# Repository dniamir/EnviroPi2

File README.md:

# EnvriPi sensor hub shield for Raspberry Pi
A Raspberry Pi shield that houses several different types of sensors
-BME280 - Bosch pressure, temperature and humidity sensor
-BME680 - Bosch pressure, humidity, temperature and VOC sensor
-TMP102 - Texas Instruments temperature sensor
-BMM150 - Bosch magnetometer
-TSL25911FN - Light intensity sensor
-ICM-20649 - Invensense 6-axis IMU (3-axis gyroscope and 3-axis accelerometer)

## Summary
This code utlizies high level functions to communicate with sensors and set their configuration for proper monitoring of an aquarium.

Unfortunately, I can't make the sub-repository for chip communication public. However that package provides a simple interface for communicating with sensors va I2C and SPI.

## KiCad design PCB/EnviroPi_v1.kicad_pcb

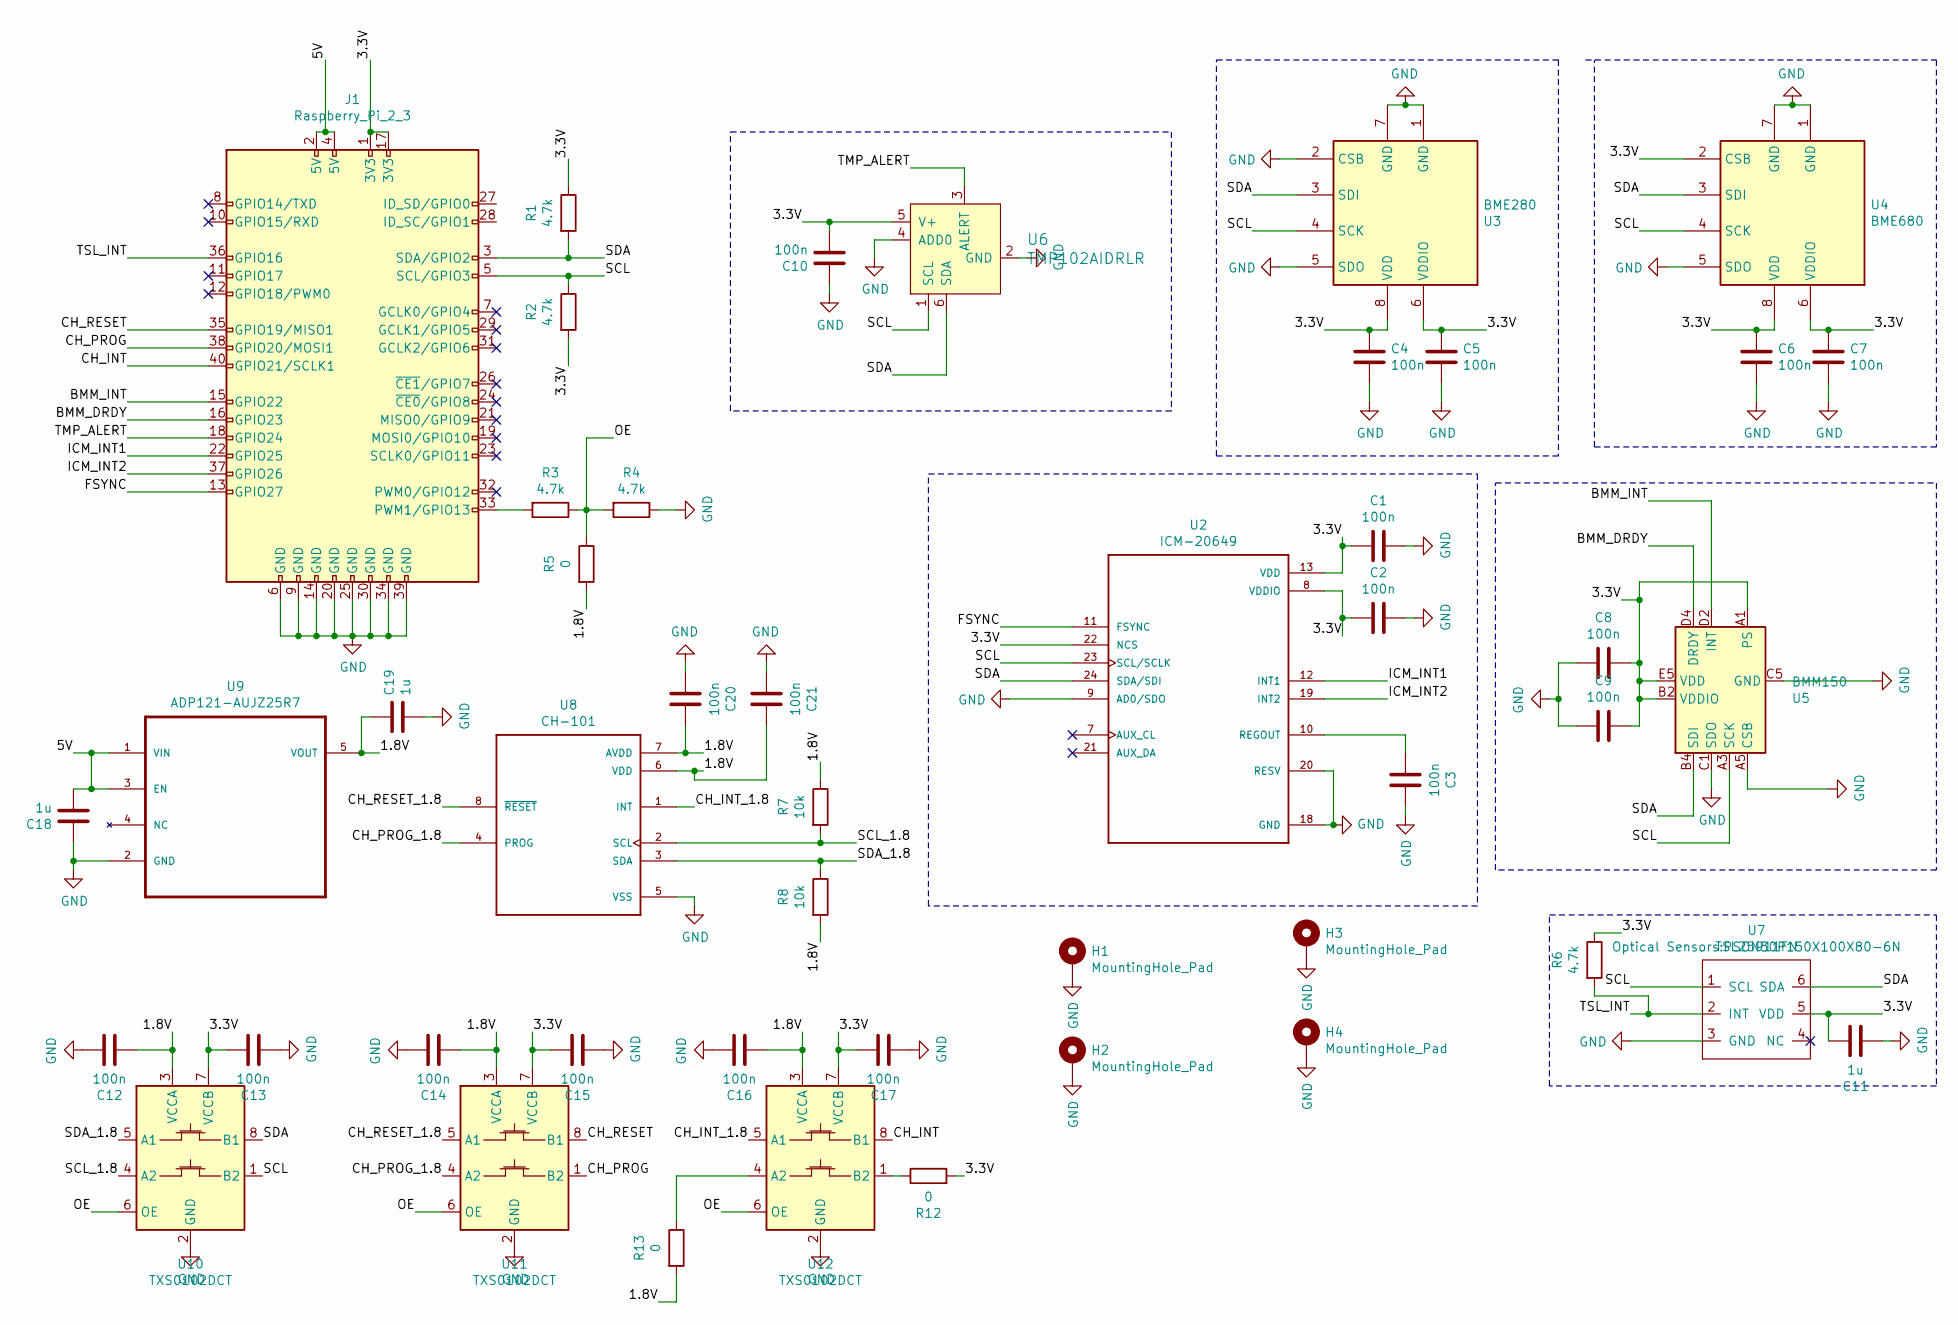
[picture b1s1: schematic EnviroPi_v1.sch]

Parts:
C1, C2, C3, C4, C5, C6, C7, C8, C9, C10, C12, C13, C14, C15, C16, C17, C20, C21: 100n; C_0805_2012Metric_Pad1.15x1.40mm_HandSolder
C11, C18, C19: 1u; C_0805_2012Metric_Pad1.15x1.40mm_HandSolder
H1, H2, H3, H4: MountingHole_Pad; MountingHole_2.5mm_Pad
J1: Raspberry_Pi_2_3; PinHeader_2x20_P2.54mm_Vertical
R1, R2, R3, R4, R6: 4.7k; R_0805_2012Metric_Pad1.15x1.40mm_HandSolder
R5, R12, R13: 0; R_0805_2012Metric_Pad1.15x1.40mm_HandSolder
R7, R8: 10k; R_0805_2012Metric_Pad1.15x1.40mm_HandSolder
U2: ICM-20649; QFN40P300X300X95-24N
U3: BME280; Bosch_LGA-8_2.5x2.5mm_P0.65mm_ClockwisePinNumbering
U4: BME680; Bosch_LGA-8_3x3mm_P0.8mm_ClockwisePinNumbering
U5: BMM150; WLCSP-12_1.56x1.56mm_P0.4mm
U6: TMP102AIDRLR; SOT50P160X60-6N; MPN TMP102AIDRLR; Digi-Key_PN 296-26834-1-ND
U7: TSL25911FN; PSON50P150X100X80-6N
U8: CH-101; XDCR_CH-101
U9: ADP121-AUJZ25R7; SOT95P280X100-5N
U10, U11, U12: TXS0102DCT; SSOP-8_2.95x2.8mm_P0.65mm

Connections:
/1.8V: C12.1, C14.1, C16.1, C19.1, C20.2, C21.2, R5.2, R7.1, R8.2, R13.2, U8.6 (VDD), U8.7 (AVDD), U9.5 (VOUT), U10.3 (VCCA), U11.3 (VCCA), U12.3 (VCCA)
/3.3V: C1.1, C2.1, C4.1, C5.1, C6.1, C7.1, C8.2, C9.2, C10.2, C11.2, C13.2, C15.2, C17.2, J1.1 (3V3), J1.17 (3V3), R1.1, R2.2, R6.1, R12.2, U2.8 (VDDIO), U2.13 (VDD), U2.22 (NCS), U3.6 (VDDIO), U3.8 (VDD), U4.2 (CSB), U4.6 (VDDIO), U4.8 (VDD), U5.A1 (PS), U5.B2 (VDDIO), U5.E5 (VDD), U6.5 (V+), U7.5 (VDD), U10.7 (VCCB), U11.7 (VCCB), U12.7 (VCCB)
/5V: C18.2, J1.2 (5V), J1.4 (5V), U9.1 (VIN), U9.3 (EN)
/BMM_DRDY: J1.16 (GPIO23), U5.D4 (DRDY)
/BMM_INT: J1.15 (GPIO22), U5.D2 (INT)
/CH_INT: J1.40 (GPIO21/SCLK1), U12.8 (B1)
/CH_INT_1.8: U8.1 (INT), U12.5 (A1)
/CH_PROG: J1.38 (GPIO20/MOSI1), U11.1 (B2)
/CH_PROG_1.8: U8.4 (PROG), U11.4 (A2)
/CH_RESET: J1.35 (GPIO19/MISO1), U11.8 (B1)
/CH_RESET_1.8: U8.8 (~RESET~), U11.5 (A1)
/FSYNC: J1.13 (GPIO27), U2.11 (FSYNC)
/ICM_INT1: J1.22 (GPIO25), U2.12 (INT1)
/ICM_INT2: J1.37 (GPIO26), U2.19 (INT2)
/OE: R3.1, R4.2, R5.1, U10.6 (OE), U11.6 (OE), U12.6 (OE)
/SCL: J1.5 (SCL/GPIO3), R2.1, U2.23 (SCL/SCLK), U3.4 (SCK), U4.4 (SCK), U5.A3 (SCK), U6.1 (SCL), U7.1 (SCL), U10.1 (B2)
/SCL_1.8: R7.2, U8.2 (SCL), U10.4 (A2)
/SDA: J1.3 (SDA/GPIO2), R1.2, U2.24 (SDA/SDI), U3.3 (SDI), U4.3 (SDI), U5.B4 (SDI), U6.6 (SDA), U7.6 (SDA), U10.8 (B1)
/SDA_1.8: R8.1, U8.3 (SDA), U10.5 (A1)
/TMP_ALERT: J1.18 (GPIO24), U6.3 (ALERT)
/TSL_INT: J1.36 (GPIO16), R6.2, U7.2 (INT)
GND: C1.2, C2.2, C3.2, C4.2, C5.2, C6.2, C7.2, C8.1, C9.1, C10.1, C11.1, C12.2, C13.1, C14.2, C15.1, C16.2, C17.1, C18.1, C19.2, C20.1, C21.1, H1.1, H2.1, H3.1, H4.1, J1.6 (GND), J1.9 (GND), J1.14 (GND), J1.20 (GND), J1.25 (GND), J1.30 (GND), J1.34 (GND), J1.39 (GND), R4.1, U2.9 (AD0/SDO), U2.18 (GND), U2.20 (RESV), U3.1 (GND), U3.2 (CSB), U3.5 (SDO), U3.7 (GND), U4.1 (GND), U4.5 (SDO), U4.7 (GND), U5.A5 (CSB), U5.C1 (SDO), U5.C5 (GND), U5.E1 (GND), U5.E3 (GND), U6.2 (GND), U6.4 (ADD0), U7.3 (GND), U8.5 (VSS), U9.2 (GND), U10.2 (GND), U11.2 (GND), U12.2 (GND)
unnamed: C3.1, U2.10 (REGOUT)
unnamed: J1.33 (PWM1/GPIO13), R3.2
unnamed: R12.1, U12.1 (B2)
unnamed: R13.1, U12.4 (A2)

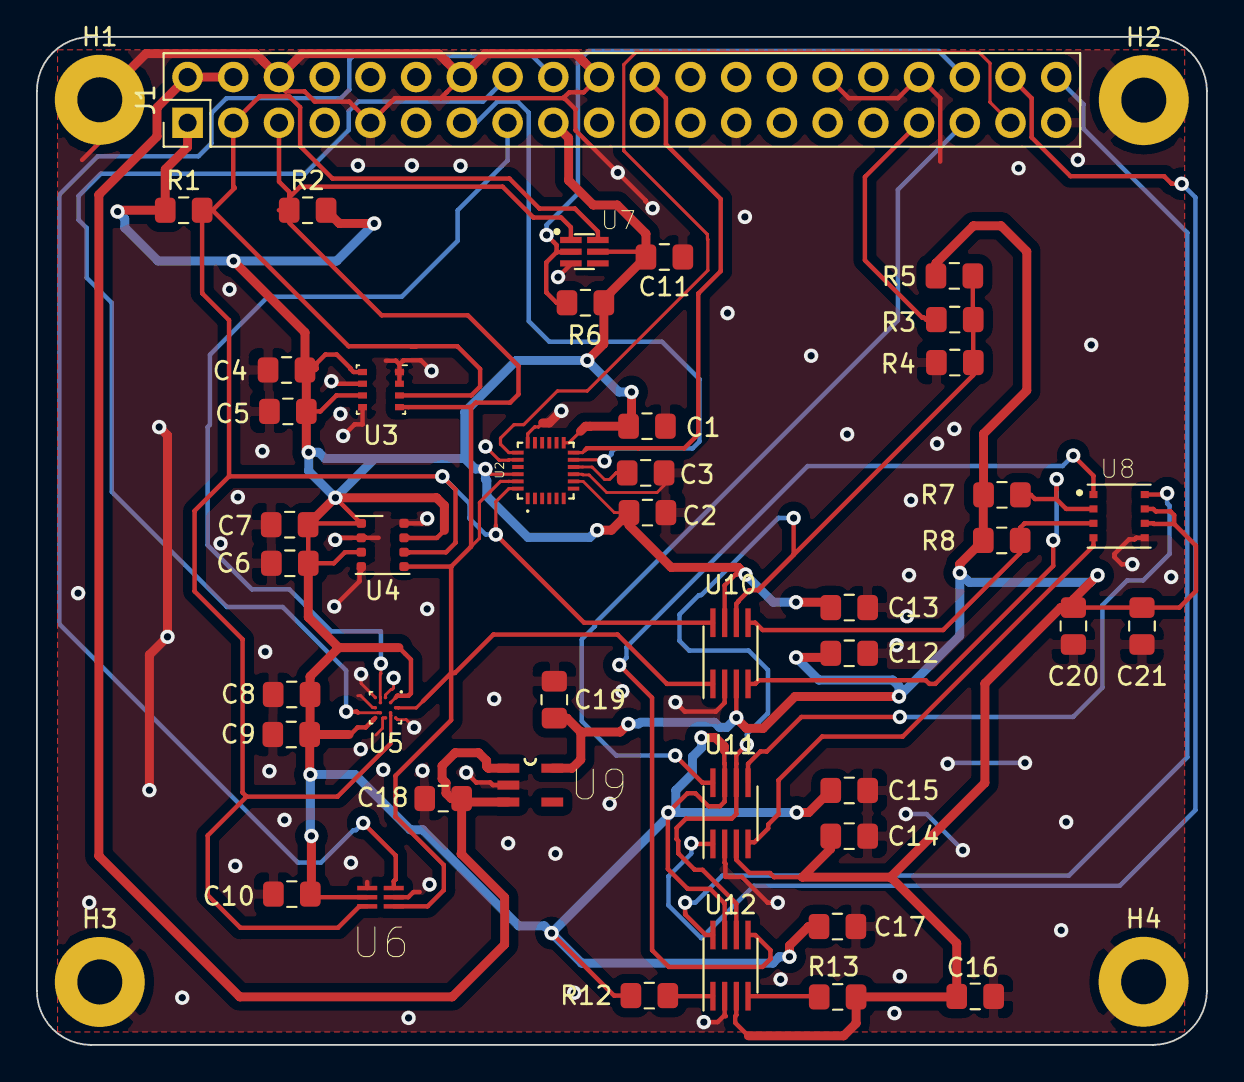
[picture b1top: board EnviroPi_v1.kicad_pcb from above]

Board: 2 copper layers, 65.0 x 56.0 mm, 47 parts (0 on the bottom side), 26 nets.

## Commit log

2020-12-13 Adding all relevant PCB files for KiCad
2020-12-13 Add readme and license files
